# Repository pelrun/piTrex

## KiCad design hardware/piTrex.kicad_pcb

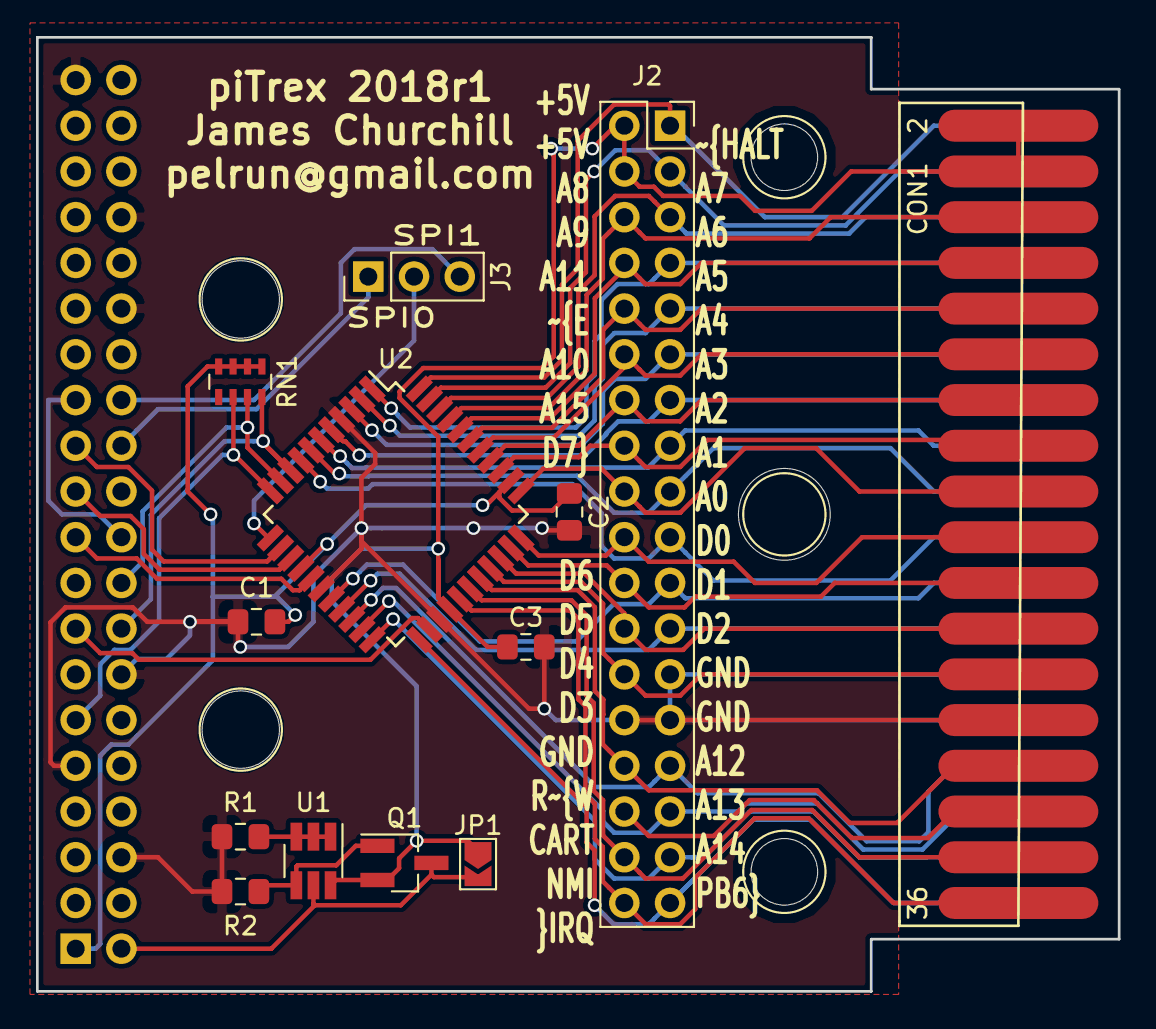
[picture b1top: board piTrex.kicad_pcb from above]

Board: 2 copper layers, 60.1 x 53.0 mm, 19 parts (1 on the bottom side), 47 nets.

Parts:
C1, C2, C3: 0.1u; C_0805_2012Metric_Pad1.15x1.40mm_HandSolder
CON1: vectrex-edge-connector; vectrex
J1: Raspberry_Pi_2_3; PiZeroHat
J2: Test; PinSocket_2x18_P2.54mm_Vertical
J3: SPI Sel; PinHeader_1x03_P2.54mm_Vertical
JP1: bypass; SolderJumper-2_P1.3mm_Open_TrianglePad1.0x1.5mm
Q1: DMG2305UX; SOT-23_Handsoldering
R1, R2: 10k; R_0805_2012Metric_Pad1.15x1.40mm_HandSolder
RN1: 47k; R_Array_Concave_4x0603
U1: DMMT5401; SOT-23-6_Handsoldering
U2: XC9572XL-VQFP44; LQFP-44_10x10mm_P0.8mm
hole1, hole2, hole3, hole4, hole5: 1pin

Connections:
+3V3: C1.1, C2.1, J1.1, RN1.1, RN1.2, RN1.3, RN1.4, U2.15, U2.35
+5V: C3.1, CON1.2, CON1.4, J2.2, J2.4, Q1.2, U1.6, U2.26
/A0: CON1.17, J2.17, U2.7
/A1: CON1.15, J2.15, U2.6
/A2: CON1.13, J2.13, U2.5
/A3: CON1.11, J2.11, U2.3
/A4: CON1.9, J2.9, U2.2
/A5: CON1.7, J2.7, U2.1
/A6: CON1.5, J2.5, U2.42
/A7: CON1.3, J2.3, U2.43
/A8: CON1.6, J2.6, U2.41
/A9: CON1.8, J2.8, U2.40
/A10: CON1.14, J2.14, U2.37
/A11: CON1.10, J2.10, U2.39
/A12: CON1.29, J2.29, U2.20
/A13: CON1.31, J2.31, U2.21
/A14: CON1.33, J2.33, U2.22
/A15: CON1.16, J2.16, U2.36
/CART: CON1.32, J2.32
/D0: CON1.19, J2.19, U2.8
/D1: CON1.21, J2.21, U2.18
/D2: CON1.23, J2.23, U2.19
/D3: CON1.26, J2.26, U2.30
/D4: CON1.24, J2.24, U2.31
/D5: CON1.22, J2.22, U2.32
/D6: CON1.20, J2.20, U2.33
/D7: CON1.18, J2.18, U2.34
/JTAG_TCK: J1.11, RN1.6, U2.11
/JTAG_TDI: J1.16, RN1.8, U2.9
/JTAG_TDO: J1.15, U2.24
/JTAG_TMS: J1.18, RN1.7, U2.10
/NMI: CON1.34, J2.34, U2.28
/R/~W: CON1.30, J2.30, U2.29
/SPI_MISO: J1.21, U2.14
/SPI_MOSI: J1.19, U2.16
/SPI_SCK: J1.23, U2.13
/VIA_PB6: CON1.35, J2.35, U2.23
/~E: CON1.12, J2.12, U2.38
/~HALT: CON1.1, J2.1, U2.44
/~IRQ: CON1.36, J2.36, U2.27
/~SPI_CE: J3.2, U2.12
/~SPI_CE0: J1.24, J3.1
/~SPI_CE1: J1.26, J3.3
GND: C1.2, C2.2, C3.2, CON1.25, CON1.27, CON1.28, J1.6, J1.9, J1.14, J1.20, J1.25, J1.30, J1.34, J1.39, J2.25, J2.27, J2.28, R1.2, R2.2, U2.4, U2.17, U2.25
unnamed: Q1.1, R2.1, U1.4
unnamed: R1.1, U1.1, U1.2, U1.3
VCC: J1.2, Q1.3, U1.5

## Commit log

2018-10-13 Initial gateware
2018-10-13 gitignore
2018-10-13 Docs
